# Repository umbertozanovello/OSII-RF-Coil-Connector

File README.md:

# OSI<sup>2</sup> compatible RF Coil Connector

This connector has been primarlily developed to interface with the [OSI<sup>2</sup> MRI LowField scanner](https://www.opensourceimaging.org/project/osii-one/). All the housing is designed to be 3D printed and the electronic boards can be manufactured by standard PCB manufacturing. Production files (e.g., Gerbers, stl, etc.) are provided as assets to the releases.

The last version of this connector features one design for the housing and for the boards. Their characteristics are described in the relevant following sections

## housing1

This housing is intended for use with one RF coil. Its shape is optimized for being eaily handed by one hand and features a locking mechanism to maintain contact in case of vibrations or minor accidental force on the cable. The system-side component provides a dust cover to protect the exposed circuitry when the RF coil is disconnected. The cover is connected to the main part of the system-side component through a hinge mechanism. The same component is supposed to be mounted on a panel that leaves access to the back part of the connector from where the cables from/to the scanner are connected. The coil-side component of the connector is made of three sub components designed to handle the connector, to secure the electronic boards and to protect the circuitry. Refer to the [assembly guide](docs/assembly-guide.md) for further information.
Four guide pins ensures the correct alignment of the coil- system-side components.

### board1

This board set features the following characteristics:
- One coaxial channel for Tx/Rx of the MR signal. This is provided by tho BNC-SMA panel adapters. Both the adapters convert a BNC to an SMA female connector supposed to be connected to the RF coil and to the Rx/Tx switch. The BNC female side is standard while the male side is a version without the Bayonet to ensure a "quick push" connection.
- Up to 36 contacts for DC or logic signals provided by an Edge Card connection.
- Implementation of the *Physical Layer* of the [MRCODS Open Standard](https://github.com/umbertozanovello/OpenStandard-CoilID/tree/main) (MRI RF Coil Open Data Standard)
- Electrically separated RF shield and Reference Ground for logical signals
- Logic and DC signals available to the scanner through a female Dsub 9 connector

## Contributors (alphabetical order)

- Nicola De Zanche
- Joshua Harper
- Jack Hayhoe
- Tri Nguyen
- Umberto Zanovello

## LICENSE
This is an open source hardware project licensed under the CERN Open Hardware Licence Version 2 - Weakly Reciprocal. For more information see the [license](./LICENSE-CERN-OHL-W) file

## CITATION
To help users correctly cite your project, a "CITATION.cff" file (read here about [citation files](https://docs.github.com/en/repositories/managing-your-repositorys-settings-and-features/customizing-your-repository/about-citation-files)) is provided with this template and can be modified according to the specific requirements.

## Acknowledgements
The connector has been developed in the framework of the project 22HLT02 A4IM. The project (22HLT02 A4IM) has received funding from the European Partnership on Metrology, co-financed by the European Union's Horizon Europe Research and Innovation Programme and by the Participating States.

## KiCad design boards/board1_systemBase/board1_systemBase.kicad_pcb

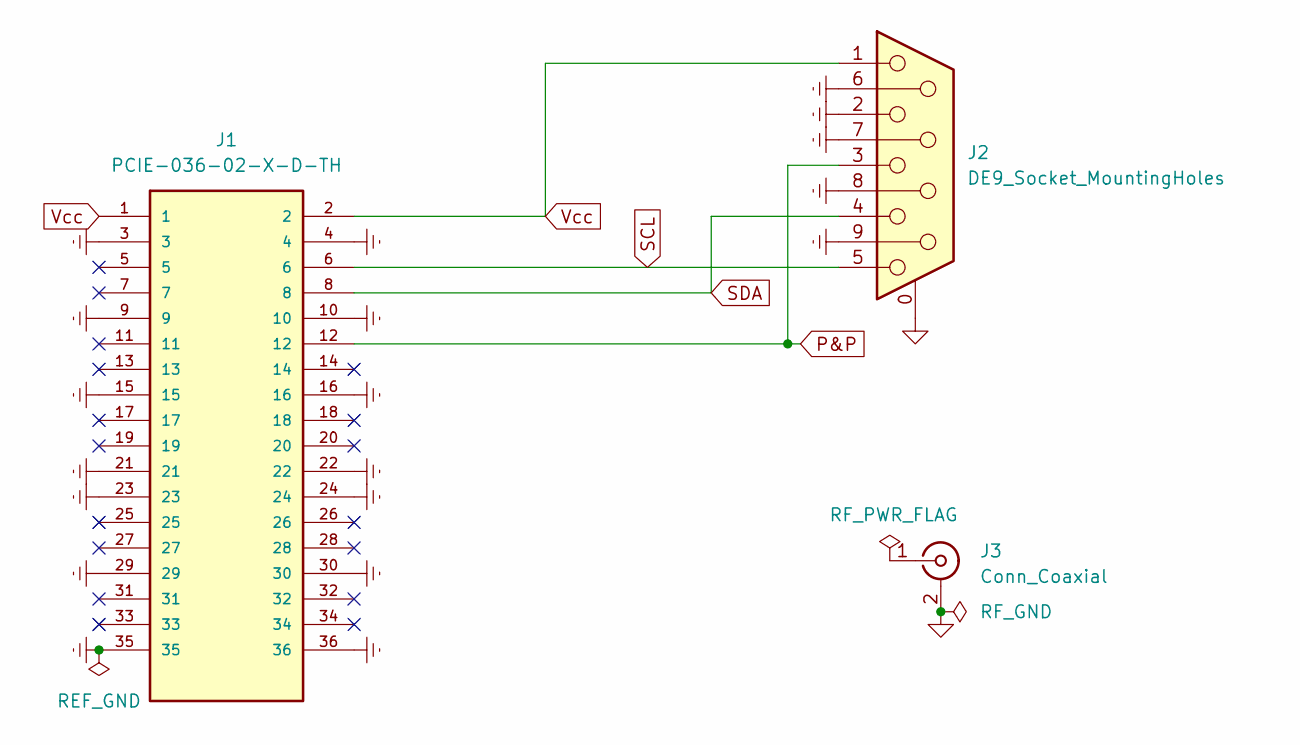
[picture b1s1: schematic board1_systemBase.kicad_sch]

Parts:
J1: PCIE-036-02-X-D-TH; SAMTEC_PCIE-036-02-X-D-TH; Manufacturer Part Number PCIE-036-02-F-D-TH; Mouser Part Number 200-PCIE03602FDTH
J2: DE9_Socket_MountingHoles; DSUB-9_Socket_Vertical_P2.77x2.84mm_MountingHoles; Manufactuer Part Number 61800929321; Mouser Part Number 710-61800929321
J3: Conn_Coaxial; femaleBNCPanel

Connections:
GNDREF: J1.3, J1.4, J1.9, J1.10, J1.15, J1.16, J1.21, J1.22, J1.23, J1.24, J1.29, J1.30, J1.35, J1.36, J2.2, J2.6, J2.7, J2.8, J2.9
GNDRF: J2.0 (PAD), J3.2 (Ext)
P&P: J1.12, J2.3
SCL: J1.6, J2.5
SDA: J1.8, J2.4
Vcc: J1.1, J1.2, J2.1

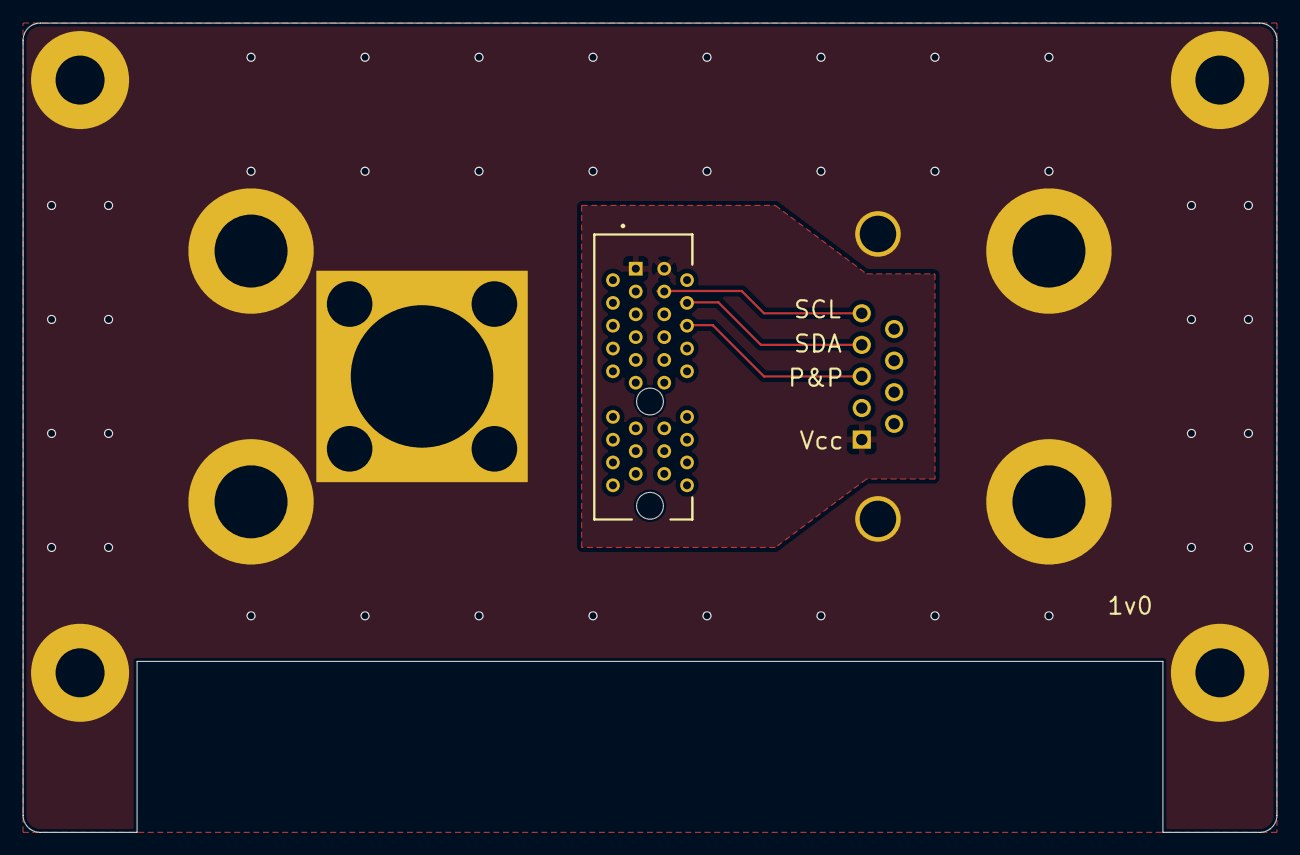
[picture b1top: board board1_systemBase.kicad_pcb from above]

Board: 2 copper layers, 110.0 x 71.0 mm, 3 parts (1 on the bottom side), 6 nets.

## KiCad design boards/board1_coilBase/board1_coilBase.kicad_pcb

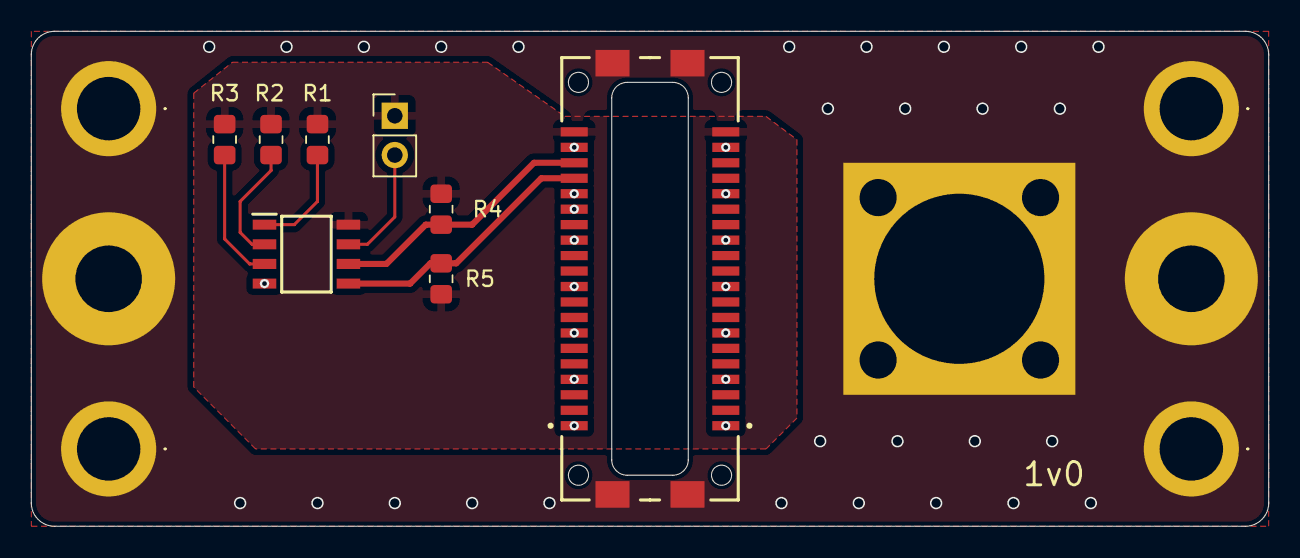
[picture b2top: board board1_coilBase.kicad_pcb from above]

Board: 2 copper layers, 80.0 x 32.0 mm, 13 parts (0 on the bottom side), 9 nets.

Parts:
EEPROM1: M24C01-RMN6P; SOIC8
J1: Double_SAL1-120-01-XX-S-A; Double_SAMTEC_SAL1-120-01-XX-S-A
J3: Conn_Coaxial; maleBNCPanel
J4: Conn_01x02_Pin; PinHeader_1x02_P2.54mm_Vertical
J**: 2239821
J**#2, J**#3, J**#4: 2239821
R1, R2, R3: 0R0; R_0805_2012Metric_Pad1.20x1.40mm_HandSolder
R4, R5: 10k0; R_0805_2012Metric_Pad1.20x1.40mm_HandSolder

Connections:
GNDREF: EEPROM1.4 (VSS), J1.3, J1.4, J1.9, J1.10, J1.12, J1.15, J1.16, J1.21, J1.22, J1.27, J1.28, J1.33, J1.34, J1.39, J1.40
GNDRF: J1.S1 (SHIELD), J1.S2 (SHIELD__1), J1.S3 (SHIELD), J1.S4 (SHIELD__1), J3.2 (Ext), J**.1, J**#2.1, J**#3.1, J**#4.1
unnamed: EEPROM1.1 (E0), R1.1
unnamed: EEPROM1.2 (E1), R2.1
unnamed: EEPROM1.3 (E2), R3.1
unnamed: EEPROM1.7 (~WC), J4.2
SCL: EEPROM1.6 (SCL), J1.6, R4.1
SDA: EEPROM1.5 (SDA), J1.8, R5.1
Vcc: EEPROM1.8 (VCC), J1.1, J1.2, J4.1, R1.2, R2.2, R3.2, R4.2, R5.2

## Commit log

2025-11-27 Updated title
2025-11-27 Updated Citation file
2025-11-27 Changed BOM file name
2025-11-28 Added Acknowledgements
2025-12-17 Modified .gitignore
2025-12-17 Reviewd dimensions for compatibility with components
2025-12-18 Modified CoilSide Centre Piece
2025-12-18 Updated CoilSide centre piece
